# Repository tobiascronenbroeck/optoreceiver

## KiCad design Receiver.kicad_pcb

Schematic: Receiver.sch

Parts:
C1: 100n 50V; C_0603_1608Metric
C2: 1u 50V; C_0603_1608Metric
C3, C4: 750p; C_0603_1608Metric
C5, C6: 820p; C_0603_1608Metric
C7: 1n; C_0603_1608Metric
C8: 100n; C_0603_1608Metric
D1: BPW34; Osram_DIL2_4.3x4.65mm_P5.08mm
D2: BAT54; D_SOT-23_ANK
D3, D4: LED; LED_0603
J1: +12V; Hirschmann_MST201
J2: -12V; Hirschmann_MST201
J3: GND; Hirschmann_MST201
J4: OUTPUT; Hirschmann_MST201
J5: Conn_01x04; Pin_Header_Straight_1x04_Pitch2.54mm
R1, R6: 24K; R_0603_1608Metric
R2, R7, R11, R12: 1K; R_0603_1608Metric
R3, R8: 100K; R_0603_1608Metric
R4, R9: 22K; R_0603_1608Metric
R5, R10: 360; R_0603_1608Metric
R13, R14: 1k; R_0603
RV1: 100K; BOURNS-3362P_pot
RV2: 50K; BOURNS-3362P_pot
U1: TL074 (ggf. durch TLV4172IPWR ersetzen); SOIC-14_3.9x8.7mm_P1.27mm

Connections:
+12V: C1.1, C2.1, D1.1 (K), J1.1, J5.2, R13.1, U1.4 (V+)
-12V: C1.2, C2.2, J2.1, J5.3, R14.1, U1.11 (V-)
/OUTPUT: C8.2, J4.1, J5.1, R12.2
GND: C7.1, C8.1, D3.1, D4.2, J3.1, J5.4, R2.1, R5.1, R7.1, R10.1, R11.2, U1.3 (+)
unnamed: C3.1, R3.2, R4.2, R6.2, U1.7
unnamed: C3.2, C4.2, R1.1, R2.2
unnamed: C4.1, R3.1, U1.6 (-)
unnamed: C5.1, D2.2, R8.2, R9.2, U1.8
unnamed: C5.2, C6.2, R6.1, R7.2
unnamed: C6.1, R8.1, U1.9 (-)
unnamed: C7.2, D2.1, U1.12 (+)
unnamed: D1.2 (A), RV1.2, U1.2 (-)
unnamed: D3.2, R13.2
unnamed: D4.1, R14.2
unnamed: R1.2, RV1.1, U1.1
unnamed: R4.1, R5.2, U1.5 (+)
unnamed: R9.1, R10.2, U1.10 (+)
unnamed: R11.1, RV2.2, U1.13 (-)
unnamed: R12.1, RV2.1, U1.14

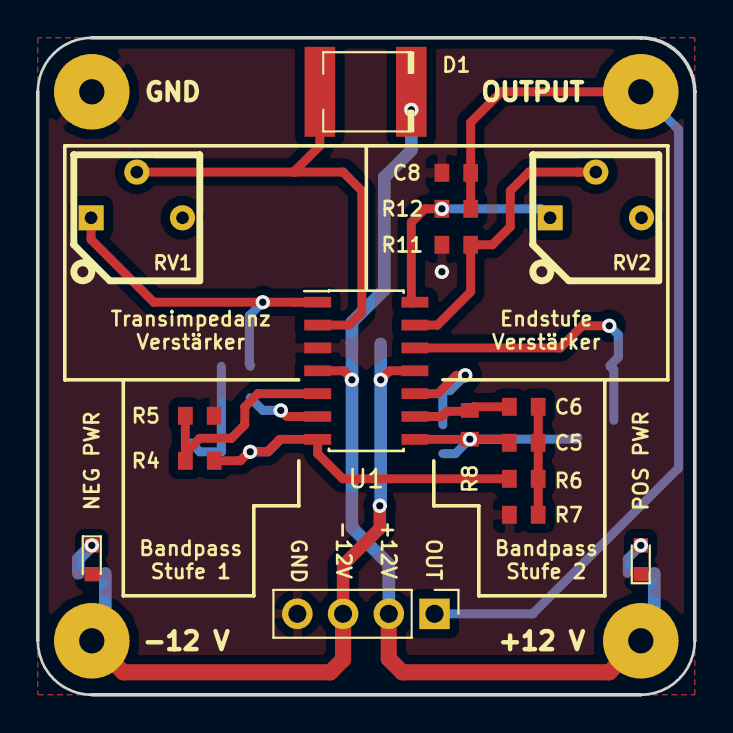
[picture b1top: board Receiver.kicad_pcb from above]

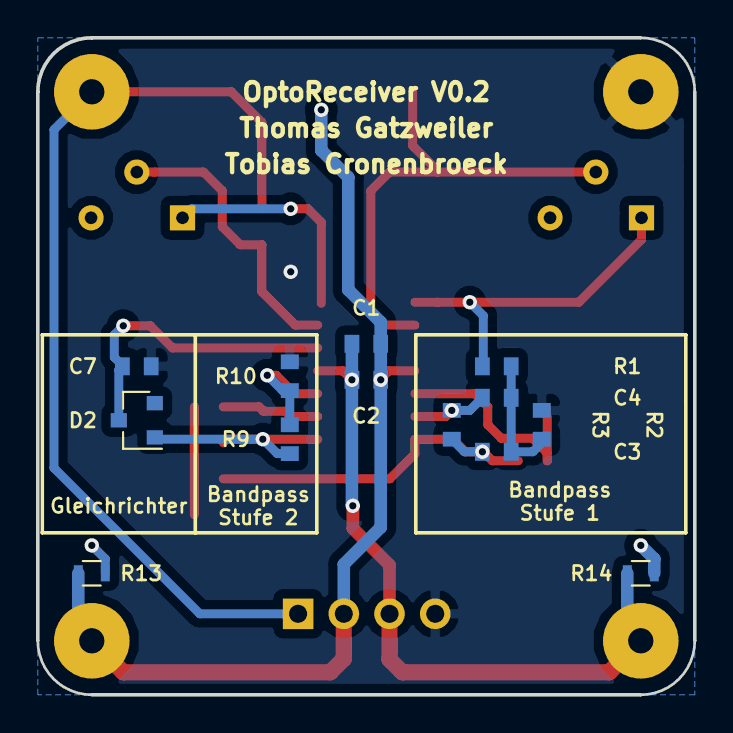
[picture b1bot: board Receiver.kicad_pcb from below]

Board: 2 copper layers, 36.5 x 36.5 mm, 34 parts (13 on the bottom side), 19 nets.

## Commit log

2018-05-03 Add LTspice simulation
2018-05-15 Add files via upload
    Netzliste erstellt und Anfang von Layout
2018-05-21 Add MST 201 banana plug to the library
2018-06-03 Update schematic and pcb
2018-06-03 Add files via upload
    - Platzierung und Silkscreen angepasst
    - 3D Modelle ergänzt
    - aktuelle Renderbilder erzeugt
2018-06-04 PCB auf Rastermaß angepasst
2018-06-04 Routing + Render Bilder erneuert
2018-06-04 3D Modell Potentiometer hinzugefügt
2018-06-25 Real Value Simulation + Update in Schematic
2018-07-01 changed values in schematic
